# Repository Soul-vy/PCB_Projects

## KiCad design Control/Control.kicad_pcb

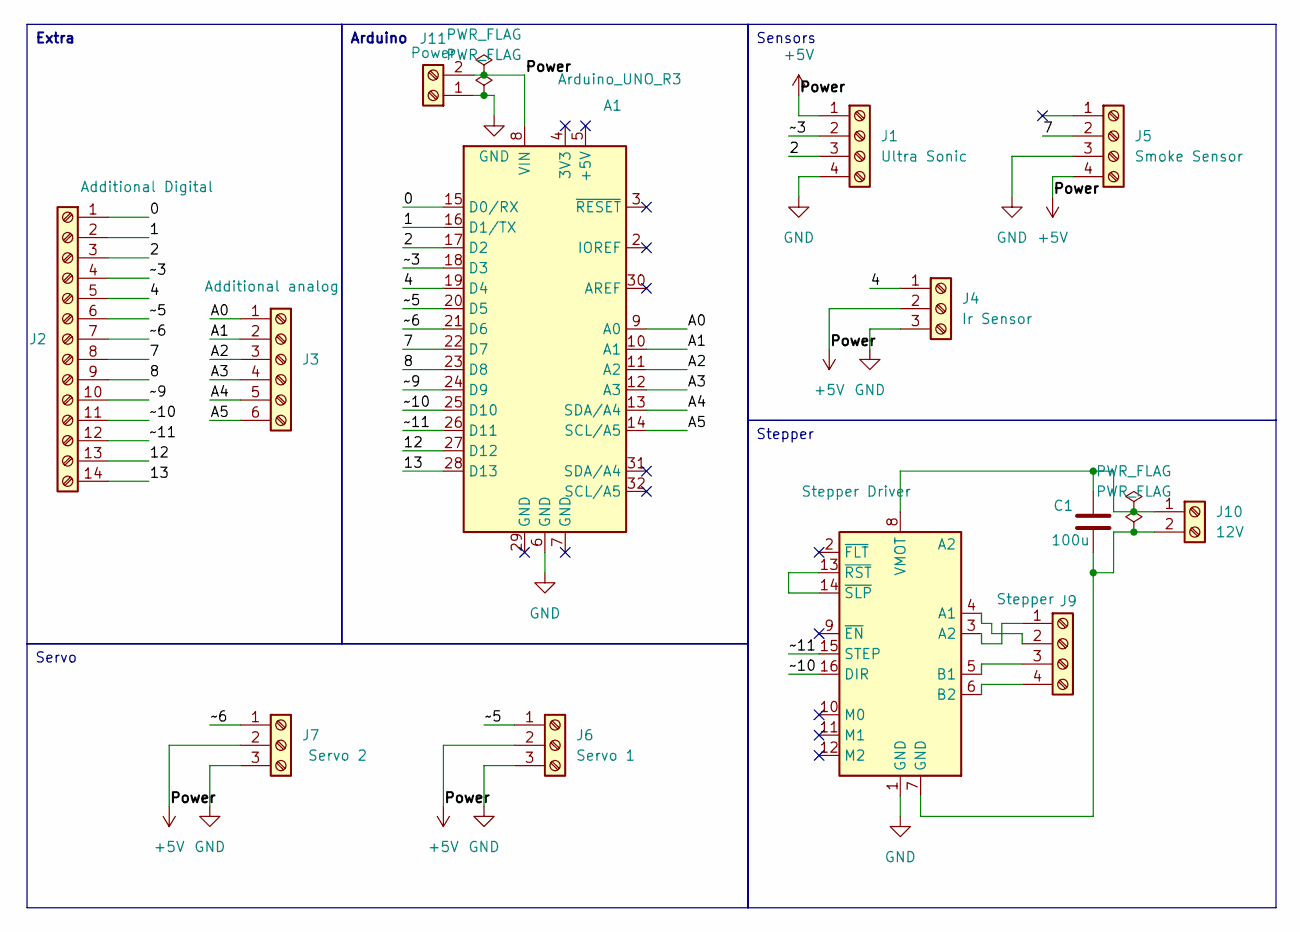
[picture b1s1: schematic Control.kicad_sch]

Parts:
A1: Arduino_UNO_R3
A2: Stepper Driver; Pololu_Breakout-16_15.2x20.3mm
C1: 100u; CP_Radial_D5.0mm_P2.00mm
J1: Ultra Sonic; TerminalBlock_Phoenix_MKDS-1,5-4-5.08_1x04_P5.08mm_Horizont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
J2: Additional Digital; TerminalBlock_Phoenix_MKDS-1,5-14-5.08_1x14_P5.08mm_Horizon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
J3: Additional analog; TerminalBlock_Phoenix_MKDS-1,5-6_1x06_P5.00mm_Horizontal
J4: Ir Sensor; TerminalBlock_Phoenix_MKDS-1,5-3_1x03_P5.00mm_Horizontal
J5: Smoke Sensor; TerminalBlock_Phoenix_MKDS-1,5-4_1x04_P5.00mm_Horizontal
J6: Servo 1; JST_EH_B3B-EH-A_1x03_P2.50mm_Vertical
J7: Servo 2; JST_EH_B3B-EH-A_1x03_P2.50mm_Vertical
J9: Stepper; JST_EH_B4B-EH-A_1x04_P2.50mm_Vertical
J10: 12V; JST_EH_B2B-EH-A_1x02_P2.50mm_Vertical
J11: Power; JST_EH_B2B-EH-A_1x02_P2.50mm_Vertical

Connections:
+5V: A1.8 (VIN), J1.1, J4.2, J5.4, J6.2, J7.2, J11.2
/0: A1.15 (D0/RX), J2.1
/1: A1.16 (D1/TX), J2.2
/2: A1.17 (D2), J1.3, J2.3
/4: A1.19 (D4), J2.5, J4.1
/7: A1.22 (D7), J2.8, J5.2
/8: A1.23 (D8), J2.9
/12: A1.27 (D12), J2.13
/13: A1.28 (D13), J2.14
/A0: A1.9 (A0), J3.1
/A1: A1.10 (A1), J3.2
/A2: A1.11 (A2), J3.3
/A3: A1.12 (A3), J3.4
/A4: A1.13 (SDA/A4), J3.5
/A5: A1.14 (SCL/A5), J3.6
/~3: A1.18 (D3), J1.2, J2.4
/~5: A1.20 (D5), J2.6, J6.1
/~6: A1.21 (D6), J2.7, J7.1
/~9: A1.24 (D9), J2.10
/~10: A1.25 (D10), A2.16 (DIR), J2.11
/~11: A1.26 (D11), A2.15 (STEP), J2.12
GND: A1.6 (GND), A2.1 (GND), J1.4, J4.3, J5.3, J6.3, J7.3, J11.1
unnamed: A2.4 (A1), J9.2
unnamed: A2.3 (A2), J9.1
unnamed: A2.5 (B1), J9.3
unnamed: A2.6 (B2), J9.4
unnamed: A2.8 (VMOT), C1.1, J10.1
unnamed: A2.13 (~RST), A2.14 (~SLP)
unnamed: A2.7 (GND), C1.2, J10.2

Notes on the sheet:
Stepper
Extra
Arduino
Sensors
Servo

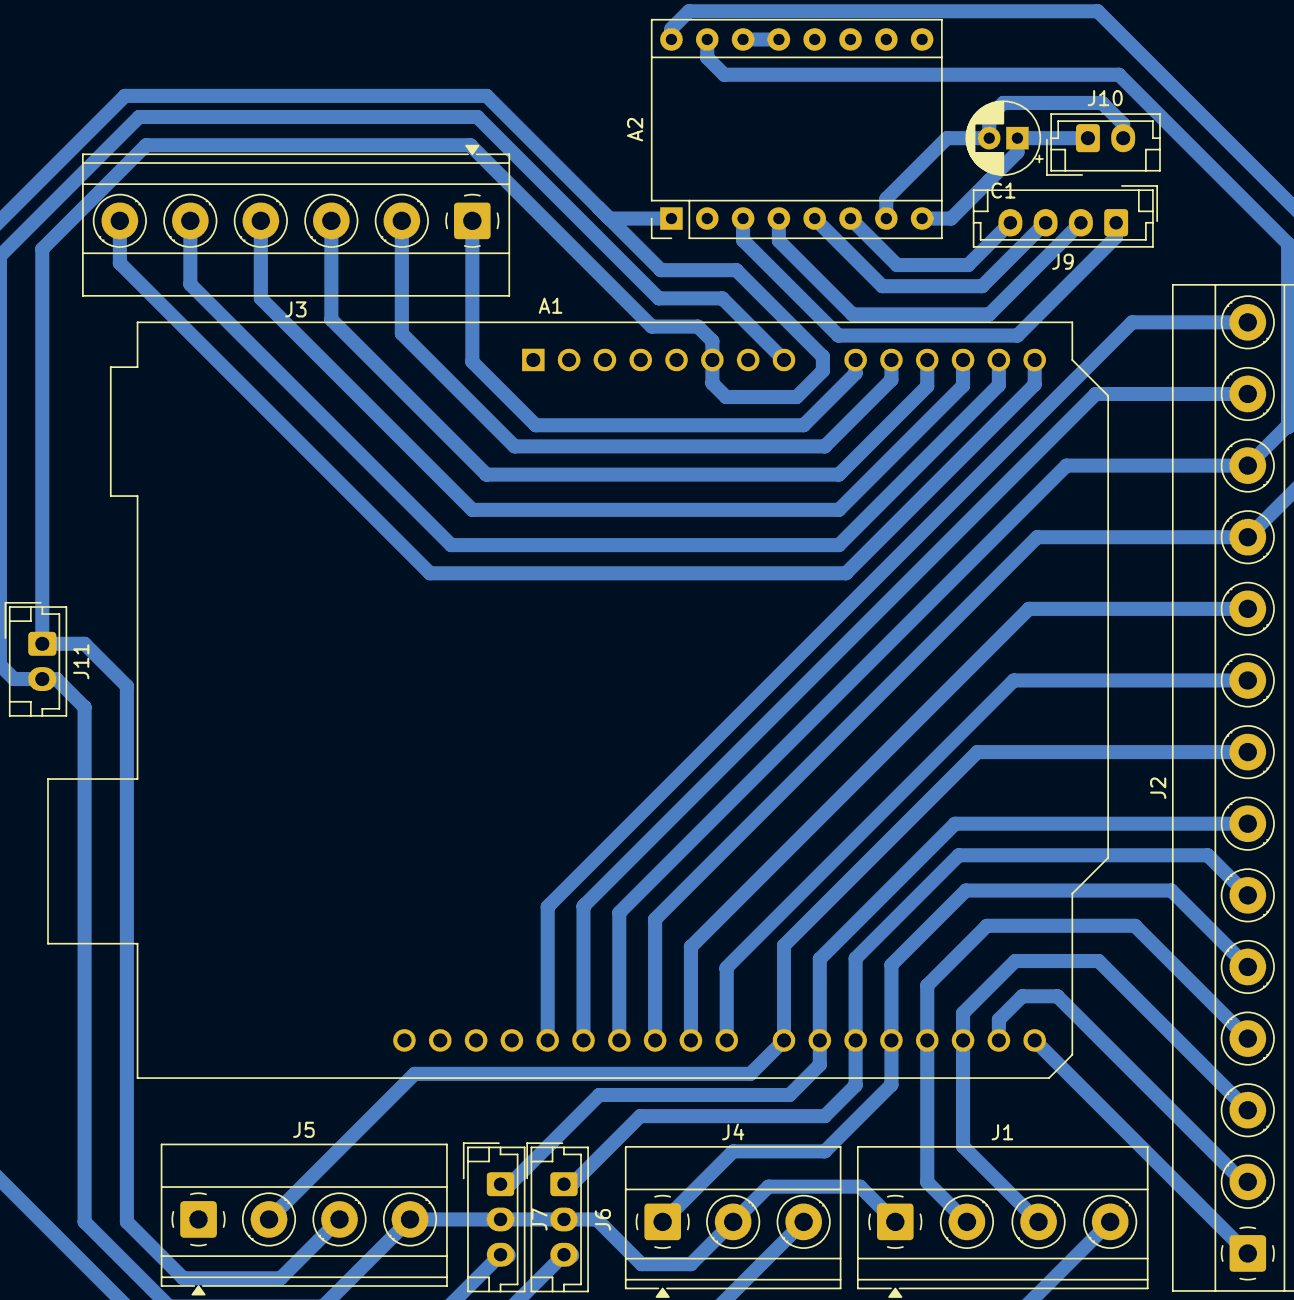
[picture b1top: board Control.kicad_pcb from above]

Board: 2 copper layers, 13 parts (0 on the bottom side), 29 nets.

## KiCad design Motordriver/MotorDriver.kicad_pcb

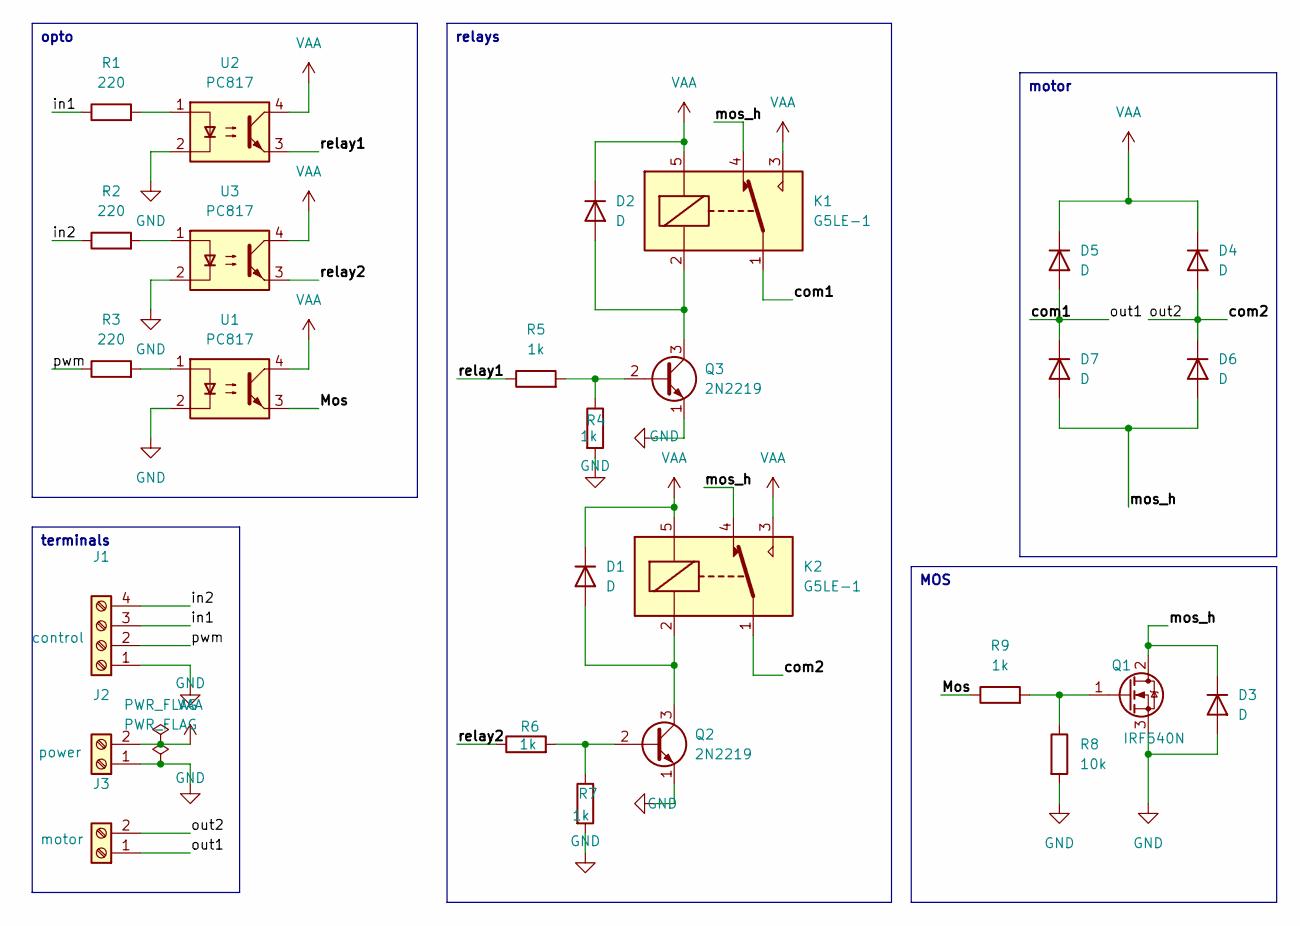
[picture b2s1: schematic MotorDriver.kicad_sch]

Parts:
D1, D2, D3, D4, D5: D; D_DO-41_SOD81_P7.62mm_Horizontal
D6, D7: D; D_DO-41_SOD81_P10.16mm_Horizontal
J1: control; TerminalBlock_Phoenix_MKDS-1,5-4-5.08_1x04_P5.08mm_Horizont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
J2: power; TerminalBlock_Phoenix_MKDS-1,5-2_1x02_P5.00mm_Horizontal
J3: motor; TerminalBlock_Phoenix_MKDS-1,5-2_1x02_P5.00mm_Horizontal
K1, K2: G5LE-1; Relay_SPDT_Omron-G5LE-1
Q1: IRF540N; TO-220-3_Vertical
Q2, Q3: 2N2219; TO-220-3_Vertical
R1, R2, R3: 220; R_Axial_DIN0207_L6.3mm_D2.5mm_P10.16mm_Horizontal
R4, R5, R6, R7, R9: 1k; R_Axial_DIN0207_L6.3mm_D2.5mm_P10.16mm_Horizontal
R8: 10k; R_Axial_DIN0207_L6.3mm_D2.5mm_P10.16mm_Horizontal
U1, U2, U3: PC817; DIP-4_W7.62mm

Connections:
/Mos: R9.1, U1.3
/com1: D5.2 (A), D7.1 (K), J3.1, K1.1
/com2: D4.2 (A), D6.1 (K), J3.2, K2.1
/in1: J1.3, R1.1
/in2: J1.4, R2.1
/mos_h: D3.1 (K), D6.2 (A), D7.2 (A), K1.4, K2.4, Q1.2 (D)
/pwm: J1.2, R3.1
/relay1: R5.1, U2.3
/relay2: R6.1, U3.3
GND: D3.2 (A), J1.1, J2.1, Q1.3 (S), Q2.1 (E), Q3.1 (E), R4.2, R7.2, R8.2, U1.2, U2.2, U3.2
unnamed: D1.2 (A), K2.2, Q2.3 (C)
unnamed: D2.2 (A), K1.2, Q3.3 (C)
unnamed: Q1.1 (G), R8.1, R9.2
unnamed: Q2.2 (B), R6.2, R7.1
unnamed: Q3.2 (B), R4.1, R5.2
unnamed: R1.2, U2.1
unnamed: R2.2, U3.1
unnamed: R3.2, U1.1
VAA: D1.1 (K), D2.1 (K), D4.1 (K), D5.1 (K), J2.2, K1.3, K1.5, K2.3, K2.5, U1.4, U2.4, U3.4

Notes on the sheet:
MOS
opto
terminals
motor
relays

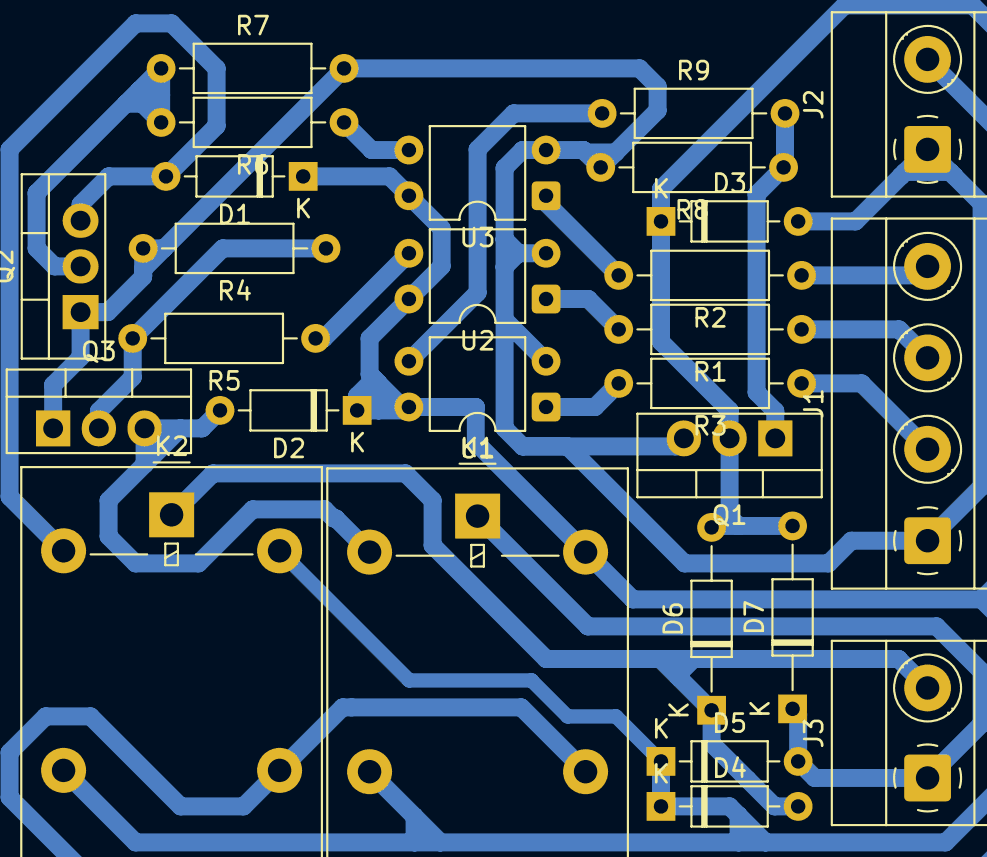
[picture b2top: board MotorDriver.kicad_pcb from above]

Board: 2 copper layers, 27 parts (0 on the bottom side), 19 nets.

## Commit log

2026-02-16 Create Motor driver
2026-04-13 Create Pcb
